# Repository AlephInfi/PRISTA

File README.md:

# PRISTA
Development repository for PRISTA (PC/104 and RS-485 Integration with Sensors Testing Assembly)

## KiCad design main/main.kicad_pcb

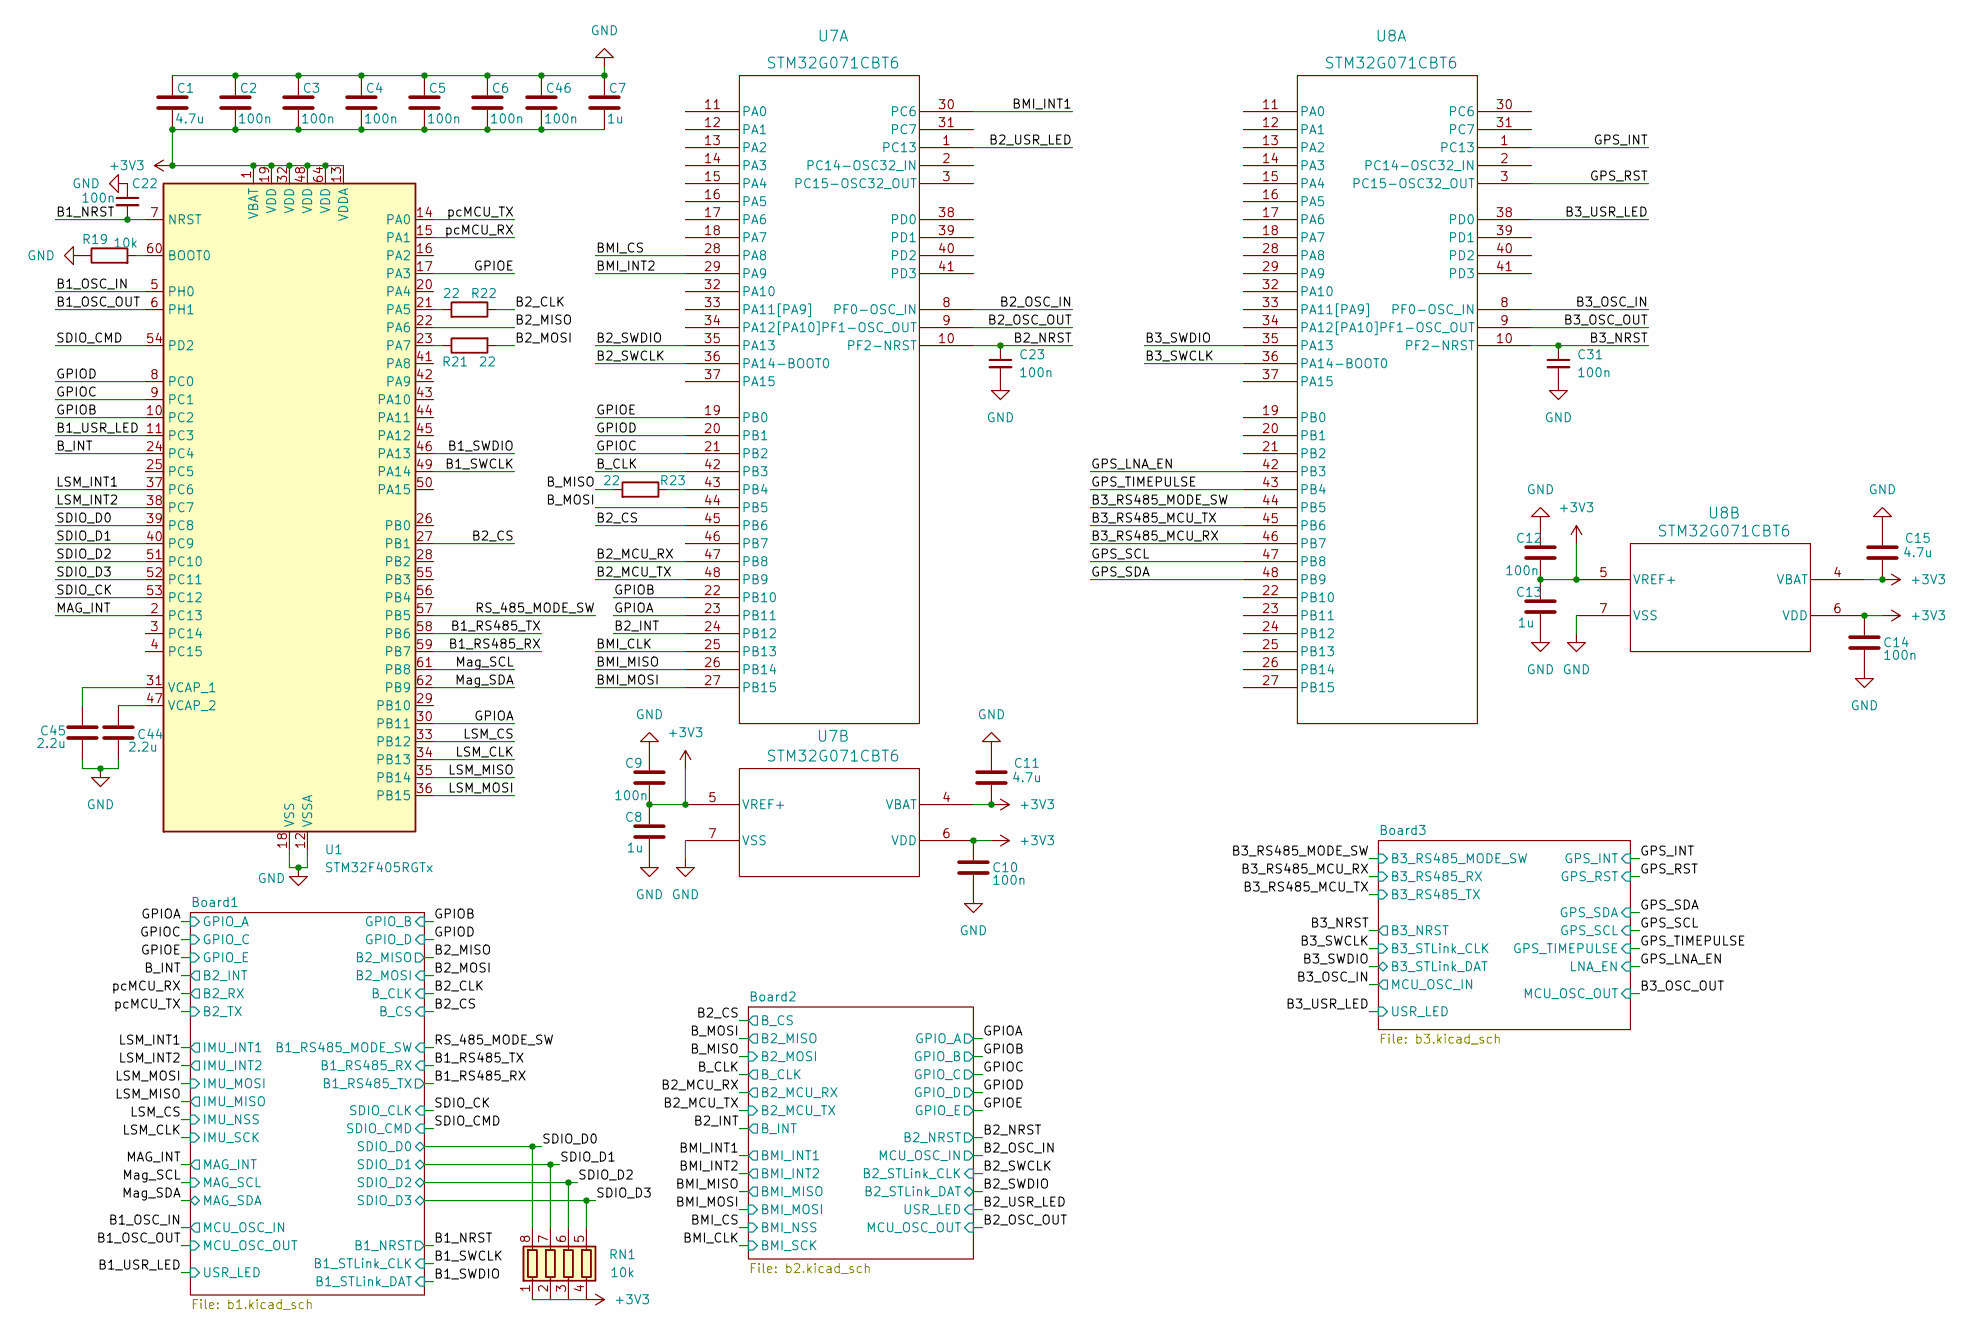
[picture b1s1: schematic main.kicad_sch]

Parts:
C1, C11, C15: 4.7u; C_0603_1608Metric
C2, C3, C4, C5, C6, C9, C10, C12, C14, C22, C23, C31, C46: 100n; C_0603_1608Metric
C7, C8, C13: 1u; C_0603_1608Metric
C44, C45: 2.2u; C_0603_1608Metric
R19: 10k; R_0603_1608Metric
R21, R22, R23: 22; R_0603_1608Metric; LCSC C23345
RN1: 10k; R_Array_Convex_4x0603; MPN UNI-ROYAL 4D03WGJ0103T5E; LCSC C29718
U1: STM32F405RGTx; LQFP-64_10x10mm_P0.5mm
U7, U8: STM32G071CBT6; LQFP-48_7x7mm_P0.5mm

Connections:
+3V3: C1.2, C2.2, C3.2, C4.2, C5.2, C6.2, C7.2, C8.1, C9.2, C10.1, C11.2, C12.2, C13.1, C14.1, C15.2, C46.2, RN1.1 (R1.1), RN1.2 (R2.1), RN1.3 (R3.1), RN1.4 (R4.1), U1.1 (VBAT), U1.13 (VDDA), U1.19 (VDD), U1.32 (VDD), U1.48 (VDD), U1.64 (VDD), U7.4 (VBAT), U7.5 (VREF+), U7.6 (VDD), U8.4 (VBAT), U8.5 (VREF+), U8.6 (VDD); also elsewhere on the board
/B1_NRST: C22.2, U1.7 (NRST); also elsewhere on the board
/B1_OSC_IN: U1.5 (PH0); also elsewhere on the board
/B1_OSC_OUT: U1.6 (PH1); also elsewhere on the board
/B1_RS485_RX: U1.59 (PB7); also elsewhere on the board
/B1_RS485_TX: U1.58 (PB6); also elsewhere on the board
/B1_SWCLK: U1.49 (PA14); also elsewhere on the board
/B1_SWDIO: U1.46 (PA13); also elsewhere on the board
/B1_USR_LED: U1.11 (PC3); also elsewhere on the board
/B2_CLK: R22.1; also elsewhere on the board
/B2_CS: U1.27 (PB1), U7.45 (PB6); also elsewhere on the board
/B2_INT: U7.24 (PB12); also elsewhere on the board
/B2_MCU_RX: U7.47 (PB8); also elsewhere on the board
/B2_MCU_TX: U7.48 (PB9); also elsewhere on the board
/B2_MISO: U1.22 (PA6); also elsewhere on the board
/B2_MOSI: R21.2; also elsewhere on the board
/B2_NRST: C23.1, U7.10 (PF2-NRST); also elsewhere on the board
/B2_OSC_IN: U7.8 (PF0-OSC_IN); also elsewhere on the board
/B2_OSC_OUT: U7.9 (PF1-OSC_OUT); also elsewhere on the board
/B2_SWCLK: U7.36 (PA14-BOOT0); also elsewhere on the board
/B2_SWDIO: U7.35 (PA13); also elsewhere on the board
/B2_USR_LED: U7.1 (PC13); also elsewhere on the board
/B3_NRST: C31.1, U8.10 (PF2-NRST); also elsewhere on the board
/B3_OSC_IN: U8.8 (PF0-OSC_IN); also elsewhere on the board
/B3_OSC_OUT: U8.9 (PF1-OSC_OUT); also elsewhere on the board
/B3_RS485_MCU_RX: U8.46 (PB7); also elsewhere on the board
/B3_RS485_MCU_TX: U8.45 (PB6); also elsewhere on the board
/B3_RS485_MODE_SW: U8.44 (PB5); also elsewhere on the board
/B3_SWCLK: U8.36 (PA14-BOOT0); also elsewhere on the board
/B3_SWDIO: U8.35 (PA13); also elsewhere on the board
/B3_USR_LED: U8.38 (PD0); also elsewhere on the board
/BMI_CLK: U7.25 (PB13); also elsewhere on the board
/BMI_CS: U7.28 (PA8); also elsewhere on the board
/BMI_INT1: U7.30 (PC6); also elsewhere on the board
/BMI_INT2: U7.29 (PA9); also elsewhere on the board
/BMI_MISO: U7.26 (PB14); also elsewhere on the board
/BMI_MOSI: U7.27 (PB15); also elsewhere on the board
/B_CLK: U7.42 (PB3); also elsewhere on the board
/B_INT: U1.24 (PC4); also elsewhere on the board
/B_MISO: R23.2; also elsewhere on the board
/B_MOSI: U7.44 (PB5); also elsewhere on the board
/GPIOA: U1.30 (PB11), U7.23 (PB11); also elsewhere on the board
/GPIOB: U1.10 (PC2), U7.22 (PB10); also elsewhere on the board
/GPIOC: U1.9 (PC1), U7.21 (PB2); also elsewhere on the board
/GPIOD: U1.8 (PC0), U7.20 (PB1); also elsewhere on the board
/GPIOE: U1.17 (PA3), U7.19 (PB0); also elsewhere on the board
/GPS_INT: U8.1 (PC13); also elsewhere on the board
/GPS_LNA_EN: U8.42 (PB3); also elsewhere on the board
/GPS_RST: U8.3 (PC15-OSC32_OUT); also elsewhere on the board
/GPS_SCL: U8.47 (PB8); also elsewhere on the board
/GPS_SDA: U8.48 (PB9); also elsewhere on the board
/GPS_TIMEPULSE: U8.43 (PB4); also elsewhere on the board
/LSM_CLK: U1.34 (PB13); also elsewhere on the board
/LSM_CS: U1.33 (PB12); also elsewhere on the board
/LSM_INT1: U1.37 (PC6); also elsewhere on the board
/LSM_INT2: U1.38 (PC7); also elsewhere on the board
/LSM_MISO: U1.35 (PB14); also elsewhere on the board
/LSM_MOSI: U1.36 (PB15); also elsewhere on the board
/MAG_INT: U1.2 (PC13); also elsewhere on the board
/Mag_SCL: U1.61 (PB8); also elsewhere on the board
/Mag_SDA: U1.62 (PB9); also elsewhere on the board
/RS_485_MODE_SW: U1.57 (PB5); also elsewhere on the board
/SDIO_CK: U1.53 (PC12); also elsewhere on the board
/SDIO_CMD: U1.54 (PD2); also elsewhere on the board
/SDIO_D0: RN1.8 (R1.2), U1.39 (PC8); also elsewhere on the board
/SDIO_D1: RN1.7 (R2.2), U1.40 (PC9); also elsewhere on the board
/SDIO_D2: RN1.6 (R3.2), U1.51 (PC10); also elsewhere on the board
/SDIO_D3: RN1.5 (R4.2), U1.52 (PC11); also elsewhere on the board
/pcMCU_RX: U1.15 (PA1); also elsewhere on the board
/pcMCU_TX: U1.14 (PA0); also elsewhere on the board
GND: C1.1, C2.1, C3.1, C4.1, C5.1, C6.1, C7.1, C8.2, C9.1, C10.2, C11.1, C12.1, C13.2, C14.2, C15.1, C22.1, C23.2, C31.2, C44.2, C45.2, C46.1, R19.1, U1.12 (VSSA), U1.18 (VSS), U1.63 (VSS), U7.7 (VSS), U8.7 (VSS); also elsewhere on the board
unnamed: R19.2, U1.60 (BOOT0)
unnamed: R22.2, U1.21 (PA5)
unnamed: R21.1, U1.23 (PA7)
unnamed: C45.1, U1.31 (VCAP_1)
unnamed: C44.1, U1.47 (VCAP_2)
unnamed: R23.1, U7.43 (PB4)

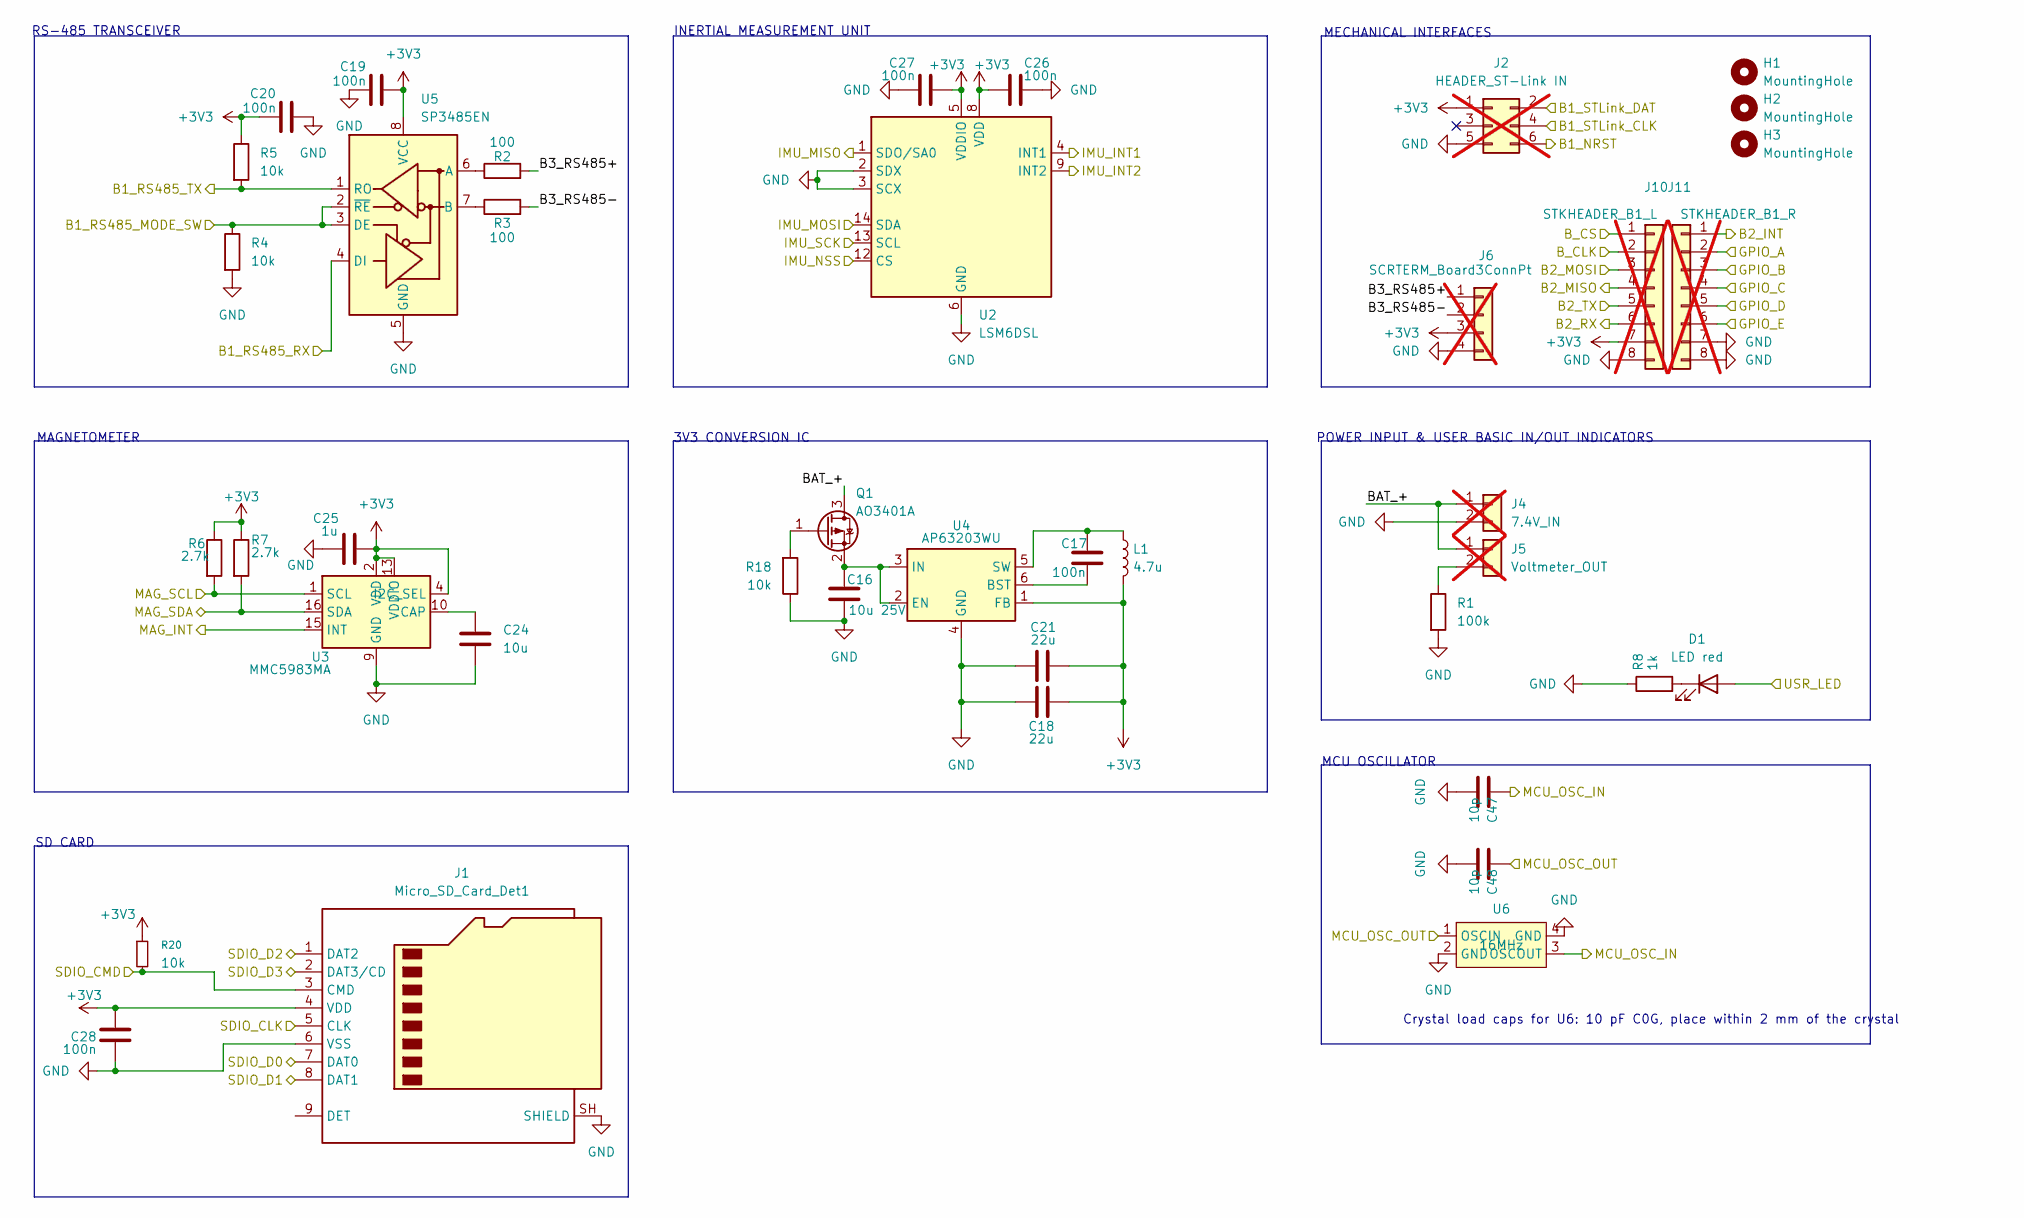
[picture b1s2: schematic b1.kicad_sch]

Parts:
C16: 10u 25V; C_0805_2012Metric; LCSC C15850
C17, C19, C20, C26, C27, C28: 100n; C_0603_1608Metric
C18, C21: 22u; C_0603_1608Metric; LCSC C59461
C24: 10u; C_0603_1608Metric
C25: 1u; C_0603_1608Metric
C47, C48: 10p; C_0603_1608Metric; LCSC C1634
D1: LED red; LED_0805_2012Metric; LCSC C84256
H1, H2, H3: MountingHole; MountingHole_3.2mm_M3
J1: Micro_SD_Card_Det1; microSD_HC_Molex_47219-2001
J2: HEADER_ST-Link IN; PinHeader_2x03_P2.54mm_Horizontal; not fitted
J4: 7.4V_IN; TerminalBlock_Phoenix_MKDS-1-2-3.81_1x02_P3.81mm_Horizontal; not fitted
J5: Voltmeter_OUT; TerminalBlock_Phoenix_MKDS-1-2-3.81_1x02_P3.81mm_Horizontal; not fitted
J6: SCRTERM_Board3ConnPt; TerminalBlock_Phoenix_MKDS-1-4-3.81_1x04_P3.81mm_Horizontal; not fitted
J10: STKHEADER_B1_R; PinHeader_1x08_P2.54mm_Vertical; not fitted
J11: STKHEADER_B1_L; PinHeader_1x08_P2.54mm_Vertical; not fitted
L1: 4.7u; L_6.3x6.3_H3
Q1: AO3401A; SOT-23; LCSC C15127
R1: 100k; R_0603_1608Metric
R2, R3: 100; R_0603_1608Metric
R4, R5, R18, R20: 10k; R_0603_1608Metric
R6, R7: 2.7k; R_0603_1608Metric
R8: 1k; R_0603_1608Metric
U2: LSM6DSL; LGA-14_3x2.5mm_P0.5mm_LayoutBorder3x4y
U3: MMC5983MA; LGA-16_3x3mm_P0.5mm
U4: AP63203WU; TSOT-23-6
U5: SP3485EN; SOIC-8_3.9x4.9mm_P1.27mm; LCSC C8963
U6: 16MHz; Crystal_SMD_3225-4Pin_3.2x2.5mm; MPN YXC X322516MLB4SI; LCSC C13738

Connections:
+3V3: C18.1, C19.2, C20.1, C21.1, C25.2, C26.1, C27.2, C28.1, J1.4 (VDD), J2.1, J6.3, J10.7, L1.2, R5.1, R6.1, R7.1, R20.1, U2.5 (VDDIO), U2.8 (VDD), U3.2 (VDD), U3.4 (I2C_SEL), U3.13 (VDDIO), U4.1 (FB), U5.8 (VCC); also elsewhere on the board
/B1_NRST: J2.6; also elsewhere on the board
/B1_OSC_IN: C47.1, U6.3 (OSCOUT); also elsewhere on the board
/B1_OSC_OUT: C48.1, U6.1 (OSCIN); also elsewhere on the board
/B1_RS485_RX: R5.2, U5.1 (RO); also elsewhere on the board
/B1_RS485_TX: U5.4 (DI); also elsewhere on the board
/B1_SWCLK: J2.4; also elsewhere on the board
/B1_SWDIO: J2.2; also elsewhere on the board
/B1_USR_LED: D1.2 (A); also elsewhere on the board
/B2_CLK: J10.2; also elsewhere on the board
/B2_CS: J10.1; also elsewhere on the board
/B2_MISO: J10.4; also elsewhere on the board
/B2_MOSI: J10.3; also elsewhere on the board
/B_INT: J11.1; also elsewhere on the board
/Board1/B3_RS485+: J6.1, R2.2
/Board1/B3_RS485-: J6.2, R3.2
/Board1/BAT_+: J4.1, J5.1, Q1.3 (D)
/GPIOA: J11.2; also elsewhere on the board
/GPIOB: J11.3; also elsewhere on the board
/GPIOC: J11.4; also elsewhere on the board
/GPIOD: J11.5; also elsewhere on the board
/GPIOE: J11.6; also elsewhere on the board
/LSM_CLK: U2.13 (SCL); also elsewhere on the board
/LSM_CS: U2.12 (CS); also elsewhere on the board
/LSM_INT1: U2.4 (INT1); also elsewhere on the board
/LSM_INT2: U2.9 (INT2); also elsewhere on the board
/LSM_MISO: U2.1 (SDO/SA0); also elsewhere on the board
/LSM_MOSI: U2.14 (SDA); also elsewhere on the board
/MAG_INT: U3.15 (INT); also elsewhere on the board
/Mag_SCL: R6.2, U3.1 (SCL); also elsewhere on the board
/Mag_SDA: R7.2, U3.16 (SDA); also elsewhere on the board
/RS_485_MODE_SW: R4.1, U5.2 (~RE), U5.3 (DE); also elsewhere on the board
/SDIO_CK: J1.5 (CLK); also elsewhere on the board
/SDIO_CMD: J1.3 (CMD), R20.2; also elsewhere on the board
/SDIO_D0: J1.7 (DAT0); also elsewhere on the board
/SDIO_D1: J1.8 (DAT1); also elsewhere on the board
/SDIO_D2: J1.1 (DAT2); also elsewhere on the board
/SDIO_D3: J1.2 (DAT3/CD); also elsewhere on the board
/pcMCU_RX: J10.6; also elsewhere on the board
/pcMCU_TX: J10.5; also elsewhere on the board
GND: C16.2, C18.2, C19.1, C20.2, C21.2, C24.2, C25.1, C26.2, C27.1, C28.2, C47.2, C48.2, J1.6 (VSS), J1.SH (SHIELD), J2.5, J4.2, J6.4, J10.8, J11.7, J11.8, R1.2, R4.2, R8.1, R18.1, U2.2 (SDX), U2.3 (SCX), U2.6 (GND), U2.7 (GND), U3.9 (GND), U3.11 (GND), U4.4 (GND), U5.5 (GND), U6.2 (GND), U6.4 (GND); also elsewhere on the board
unnamed: D1.1 (K), R8.2
unnamed: J5.2, R1.1
unnamed: Q1.1 (G), R18.2
unnamed: C16.1, Q1.2 (S), U4.2 (EN), U4.3 (IN)
unnamed: C24.1, U3.10 (CAP)
unnamed: C17.2, U4.6 (BST)
unnamed: C17.1, L1.1, U4.5 (SW)
unnamed: R2.1, U5.6 (A)
unnamed: R3.1, U5.7 (B)

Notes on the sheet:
INERTIAL MEASUREMENT UNIT
MAGNETOMETER
Crystal load caps for U6: 10 pF C0G, place within 2 mm of the crystal
POWER INPUT & USER BASIC IN/OUT INDICATORS
MCU OSCILLATOR
RS-485 TRANSCEIVER
SD CARD
3V3 CONVERSION IC
MECHANICAL INTERFACES

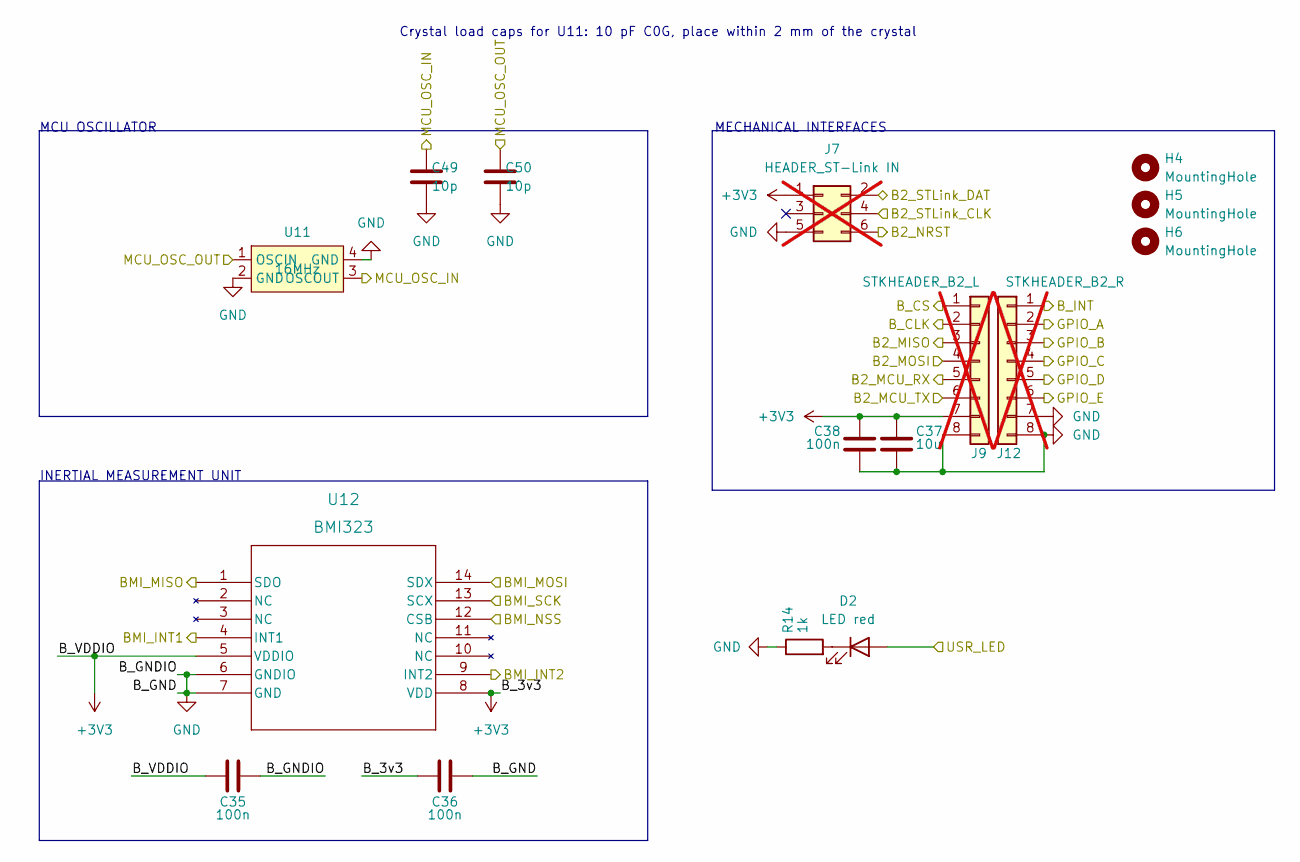
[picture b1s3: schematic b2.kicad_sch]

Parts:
C35, C36, C38: 100n; C_0603_1608Metric
C37: 10u; C_0603_1608Metric
C49, C50: 10p; C_0603_1608Metric; LCSC C1634
D2: LED red; LED_0805_2012Metric; LCSC C84256
H4, H5, H6: MountingHole; MountingHole_3.2mm_M3
J7: HEADER_ST-Link IN; PinHeader_2x03_P2.54mm_Horizontal; not fitted
J9: STKHEADER_B2_L; PinSocket_1x08_P2.54mm_Vertical; not fitted
J12: STKHEADER_B2_R; PinSocket_1x08_P2.54mm_Vertical; not fitted
R14: 1k; R_0603_1608Metric
U11: 16MHz; Crystal_SMD_3225-4Pin_3.2x2.5mm; MPN YXC X322516MLB4SI; LCSC C13738
U12: BMI323; BMI323_BOS

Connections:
+3V3: C35.1, C36.1, C37.1, C38.1, J7.1, J9.7, U12.5 (VDDIO), U12.8 (VDD); also elsewhere on the board
/B2_CS: J9.1; also elsewhere on the board
/B2_INT: J12.1; also elsewhere on the board
/B2_MCU_RX: J9.5; also elsewhere on the board
/B2_MCU_TX: J9.6; also elsewhere on the board
/B2_NRST: J7.6; also elsewhere on the board
/B2_OSC_IN: C49.1, U11.3 (OSCOUT); also elsewhere on the board
/B2_OSC_OUT: C50.1, U11.1 (OSCIN); also elsewhere on the board
/B2_SWCLK: J7.4; also elsewhere on the board
/B2_SWDIO: J7.2; also elsewhere on the board
/B2_USR_LED: D2.2 (A); also elsewhere on the board
/BMI_CLK: U12.13 (SCX); also elsewhere on the board
/BMI_CS: U12.12 (CSB); also elsewhere on the board
/BMI_INT1: U12.4 (INT1); also elsewhere on the board
/BMI_INT2: U12.9 (INT2); also elsewhere on the board
/BMI_MISO: U12.1 (SDO); also elsewhere on the board
/BMI_MOSI: U12.14 (SDX); also elsewhere on the board
/B_CLK: J9.2; also elsewhere on the board
/B_MISO: J9.4; also elsewhere on the board
/B_MOSI: J9.3; also elsewhere on the board
/GPIOA: J12.2; also elsewhere on the board
/GPIOB: J12.3; also elsewhere on the board
/GPIOC: J12.4; also elsewhere on the board
/GPIOD: J12.5; also elsewhere on the board
/GPIOE: J12.6; also elsewhere on the board
GND: C35.2, C36.2, C37.2, C38.2, C49.2, C50.2, J7.5, J9.8, J12.7, J12.8, R14.1, U11.2 (GND), U11.4 (GND), U12.6 (GNDIO), U12.7 (GND); also elsewhere on the board
unnamed: D2.1 (K), R14.2

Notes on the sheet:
INERTIAL MEASUREMENT UNIT
MCU OSCILLATOR
Crystal load caps for U11: 10 pF C0G, place within 2 mm of the crystal
MECHANICAL INTERFACES

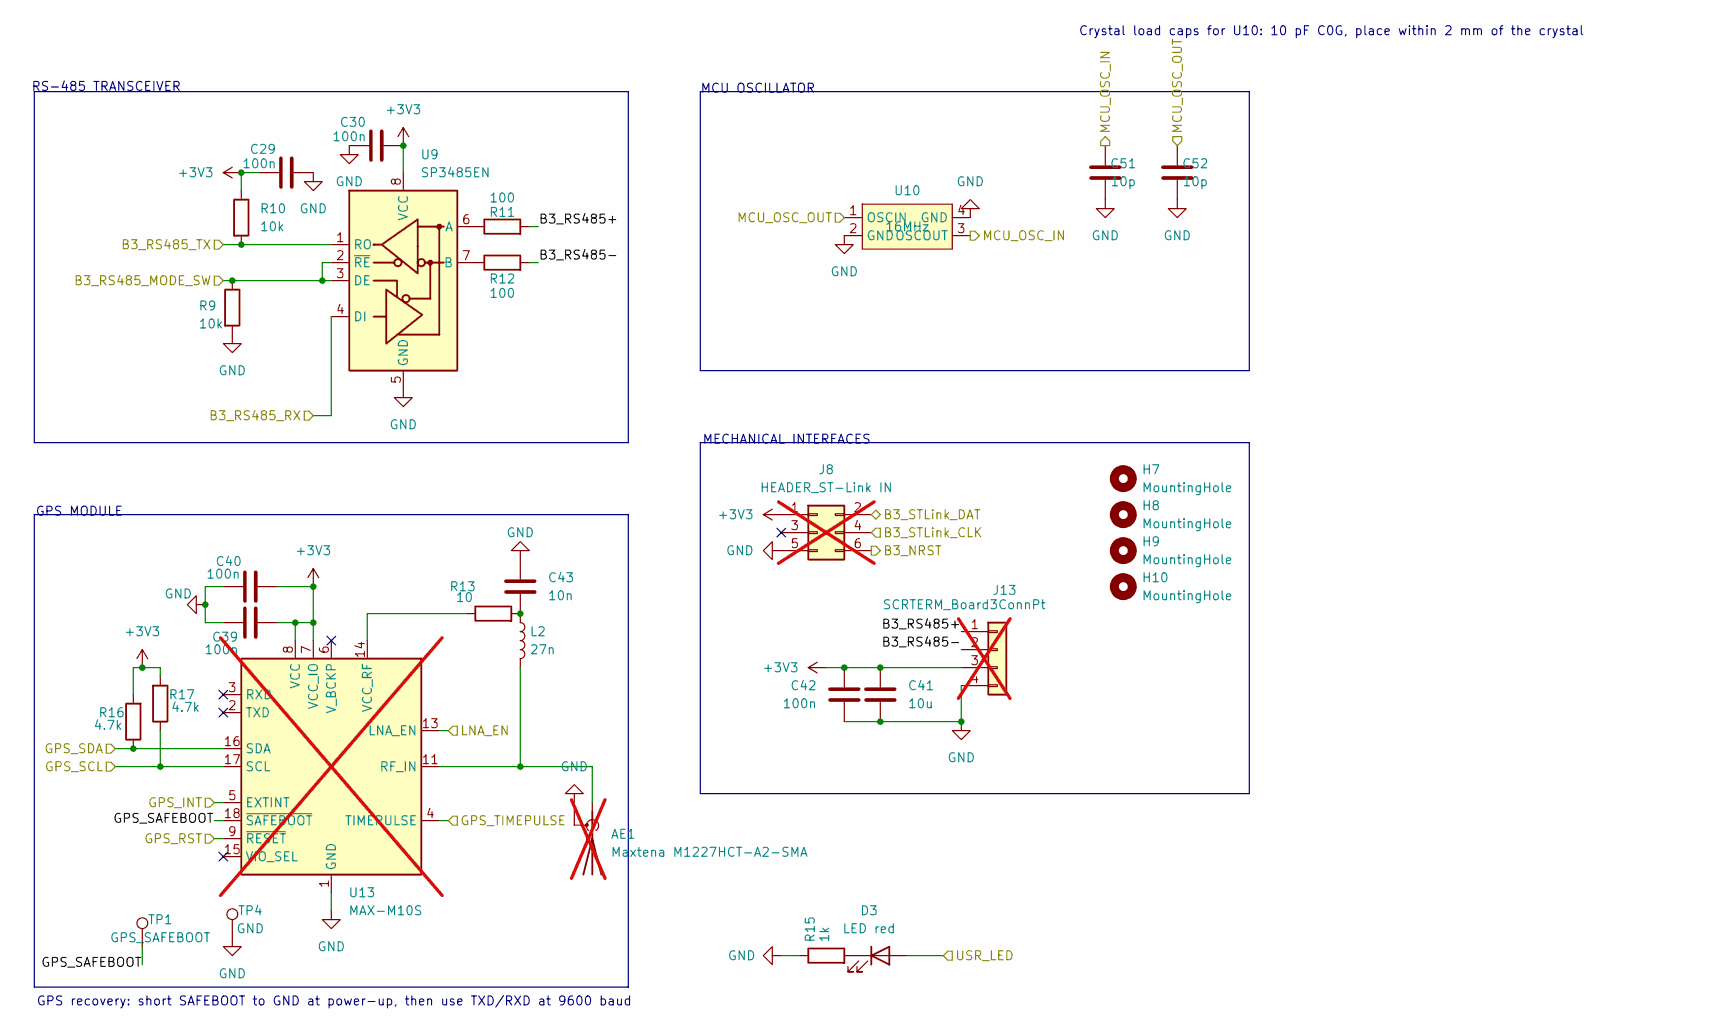
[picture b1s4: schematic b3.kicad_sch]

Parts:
AE1: Maxtena M1227HCT-A2-SMA; SMA_Amphenol_132289_EdgeMount; not fitted
C29, C30, C39, C40, C42: 100n; C_0603_1608Metric
C41: 10u; C_0603_1608Metric
C43: 10n; C_0603_1608Metric
C51, C52: 10p; C_0603_1608Metric; LCSC C1634
D3: LED red; LED_0805_2012Metric; LCSC C84256
H7, H8, H9, H10: MountingHole; MountingHole_3.2mm_M3
J8: HEADER_ST-Link IN; PinHeader_2x03_P2.54mm_Horizontal; not fitted
J13: SCRTERM_Board3ConnPt; TerminalBlock_Phoenix_MKDS-1-4-3.81_1x04_P3.81mm_Horizontal; not fitted
L2: 27n; L_0603_1608Metric
R9, R10: 10k; R_0603_1608Metric
R11, R12: 100; R_0603_1608Metric
R13: 10; R_0603_1608Metric
R15: 1k; R_0603_1608Metric
R16, R17: 4.7k; R_0603_1608Metric
TP1: GPS_SAFEBOOT; TestPoint_Pad_D1.0mm
TP4: GND; TestPoint_Pad_D1.0mm
U9: SP3485EN; SOIC-8_3.9x4.9mm_P1.27mm; LCSC C8963
U10: 16MHz; Crystal_SMD_3225-4Pin_3.2x2.5mm; MPN YXC X322516MLB4SI; LCSC C13738
U13: MAX-M10S; ublox_MAX; not fitted

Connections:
+3V3: C29.1, C30.2, C39.1, C40.1, C41.1, C42.1, J8.1, J13.3, R10.1, R16.2, R17.2, U9.8 (VCC), U13.7 (VCC_IO), U13.8 (VCC); also elsewhere on the board
/B3_NRST: J8.6; also elsewhere on the board
/B3_OSC_IN: C51.1, U10.3 (OSCOUT); also elsewhere on the board
/B3_OSC_OUT: C52.1, U10.1 (OSCIN); also elsewhere on the board
/B3_RS485_MCU_RX: U9.4 (DI); also elsewhere on the board
/B3_RS485_MCU_TX: R10.2, U9.1 (RO); also elsewhere on the board
/B3_RS485_MODE_SW: R9.1, U9.2 (~RE), U9.3 (DE); also elsewhere on the board
/B3_SWCLK: J8.4; also elsewhere on the board
/B3_SWDIO: J8.2; also elsewhere on the board
/B3_USR_LED: D3.2 (A); also elsewhere on the board
/Board3/B3_RS485+: J13.1, R11.2
/Board3/B3_RS485-: J13.2, R12.2
/Board3/GPS_SAFEBOOT: TP1.1 (1_1), U13.18 (~SAFEBOOT)
/GPS_INT: U13.5 (EXTINT); also elsewhere on the board
/GPS_LNA_EN: U13.13 (LNA_EN); also elsewhere on the board
/GPS_RST: U13.9 (~RESET); also elsewhere on the board
/GPS_SCL: R17.1, U13.17 (SCL); also elsewhere on the board
/GPS_SDA: R16.1, U13.16 (SDA); also elsewhere on the board
/GPS_TIMEPULSE: U13.4 (TIMEPULSE); also elsewhere on the board
GND: AE1.2 (Shield), C29.2, C30.1, C39.2, C40.2, C41.2, C42.2, C43.1, C51.2, C52.2, J8.5, J13.4, R9.2, R15.1, TP4.1 (1_1), U9.5 (GND), U10.2 (GND), U10.4 (GND), U13.1 (GND), U13.10 (GND), U13.12 (GND); also elsewhere on the board
unnamed: AE1.1 (A), L2.2, U13.11 (RF_IN)
unnamed: C43.2, L2.1, R13.2
unnamed: D3.1 (K), R15.2
unnamed: R11.1, U9.6 (A)
unnamed: R12.1, U9.7 (B)
unnamed: R13.1, U13.14 (VCC_RF)

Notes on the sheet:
RS-485 TRANSCEIVER
GPS MODULE
Crystal load caps for U10: 10 pF C0G, place within 2 mm of the crystal
GPS recovery: short SAFEBOOT to GND at power-up, then use TXD/RXD at 9600 baud
MECHANICAL INTERFACES
MCU OSCILLATOR

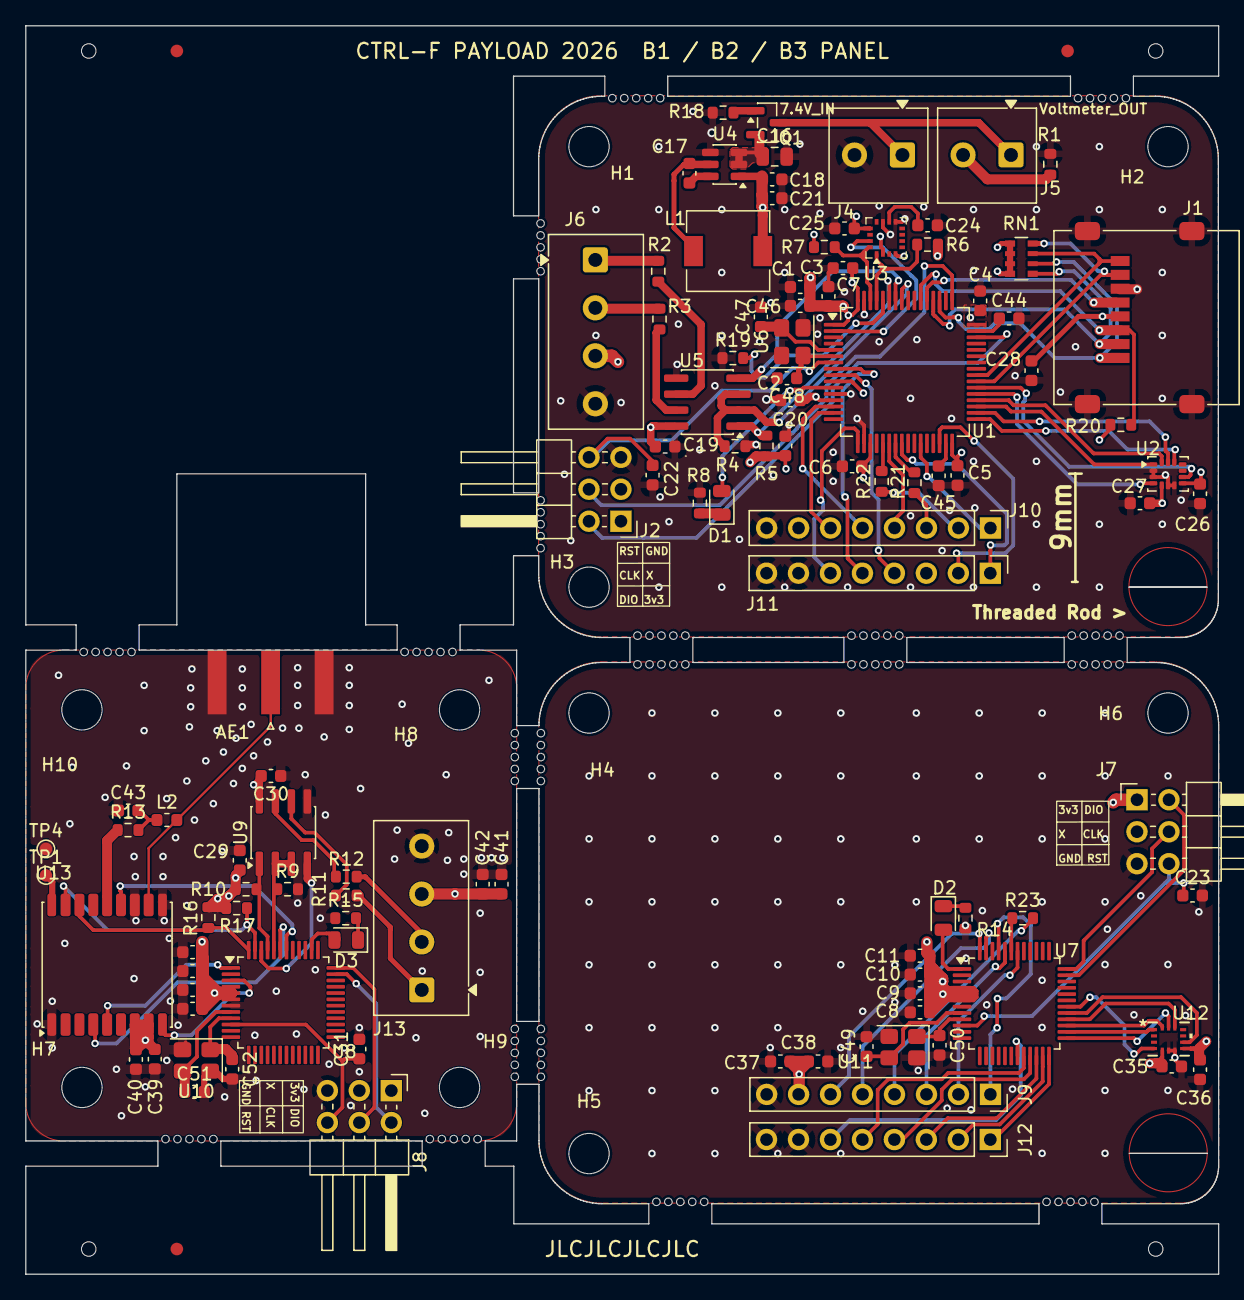
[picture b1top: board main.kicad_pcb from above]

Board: 4 copper layers, 94.8 x 99.2 mm, 139 parts (0 on the bottom side), 99 nets.

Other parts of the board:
FID1, FID2, FID3: Fiducial; Fiducial_1mm_Mask2mm
MB1: R-B1a; MouseBite
MB2: R-B1b; MouseBite
MB3: F-B1a; MouseBite
MB4: F-B1b; MouseBite
MB5: B1-B2a; MouseBite
MB6: B1-B2b; MouseBite
MB7: B1-B2c; MouseBite
MB8: B2-Ra; MouseBite
MB9: B2-Rb; MouseBite
MB10: B3-B2a; MouseBite
MB11: B3-B2b; MouseBite
MB12: F-B3a; MouseBite
MB13: F-B3b; MouseBite
MB14: B3-Fa; MouseBite
MB15: B3-Fb; MouseBite
TH1, TH2, TH3, TH4: Tooling; ToolingHole_1.152mm

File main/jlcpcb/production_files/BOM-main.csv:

Comment,Designator,Footprint,LCSC,Quantity
10,R13,R_0603_1608Metric,C22859,1
100,"R11,R12,R2,R3",R_0603_1608Metric,C22775,4
100k,R1,R_0603_1608Metric,C25803,1
100n,"C10,C12,C14,C17,C19,C2,C20,C22,C23,C26,C27,C28,C29,C3,C30,C31,C35,C36,C38,C39,C4,C40,C42,C46,C5,C6,C9",C_0603_1608Metric,C14663,27
10k,"R10,R18,R19,R20,R4,R5,R9",R_0603_1608Metric,C25804,7
10k,RN1,R_Array_Convex_4x0603,C29718,1
10n,C43,C_0603_1608Metric,C57112,1
10p,"C47,C48,C49,C50,C51,C52",C_0603_1608Metric,C1634,6
10u,"C24,C37,C41",C_0603_1608Metric,C19702,3
10u 25V,C16,C_0805_2012Metric,C15850,1
16MHz,"U10,U11,U6",Crystal_SMD_3225-4Pin_3.2x2.5mm,C13738,3
1k,"R14,R15,R8",R_0603_1608Metric,C21190,3
1u,"C13,C25,C7,C8",C_0603_1608Metric,C15849,4
2.2u,"C44,C45",C_0603_1608Metric,C23630,2
2.7k,"R6,R7",R_0603_1608Metric,C13167,2
22,"R21,R22,R23",R_0603_1608Metric,C23345,3
22u,"C18,C21",C_0603_1608Metric,C59461,2
27n,L2,L_0603_1608Metric,C12669,1
4.7k,"R16,R17",R_0603_1608Metric,C23162,2
4.7u,L1,L_6.3x6.3_H3,C128688,1
4.7u,"C1,C11,C15",C_0603_1608Metric,C19666,3
AO3401A,Q1,SOT-23,C15127,1
AP63203WU,U4,TSOT-23-6,C780769,1
BMI323,U12,BMI323_BOS,C5368700,1
LED red,"D1,D2,D3",LED_0805_2012Metric,C84256,3
LSM6DSL,U2,LGA-14_3x2.5mm_P0.5mm_LayoutBorder3x4y,C126672,1
MMC5983MA,U3,LGA-16_3x3mm_P0.5mm,C404329,1
Micro_SD_Card_Det1,J1,microSD_HC_Molex_47219-2001,C164170,1
SP3485EN,"U5,U9",SOIC-8_3.9x4.9mm_P1.27mm,C8963,2
STM32F405RGTx,U1,LQFP-64_10x10mm_P0.5mm,C15742,1
STM32G071CBT6,"U7,U8",LQFP-48_7x7mm_P0.5mm,C432212,2

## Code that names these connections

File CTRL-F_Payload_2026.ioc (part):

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Mcu.Name=STM32F405RGTx
Mcu.Package=LQFP64
Mcu.UserName=STM32F405RGTx
PA0-WKUP.GPIOParameters=GPIO_Label
PA0-WKUP.GPIO_Label=PCTX
PA0-WKUP.Mode=Asynchronous
PA0-WKUP.Signal=UART4_TX
PA1.GPIOParameters=GPIO_Label
PA1.GPIO_Label=PCRX
PA1.Mode=Asynchronous
PA1.Signal=UART4_RX
PA13.Mode=Serial_Wire
PA13.Signal=SYS_JTMS-SWDIO
PA14.Mode=Serial_Wire
PA14.Signal=SYS_JTCK-SWCLK
PA15.GPIOParameters=GPIO_Label
PA15.GPIO_Label=SD_Detect
PA15.Signal=GPXTI15
PA3.GPIOParameters=GPIO_Label
PA3.GPIO_Label=GPIO_E
PA3.Signal=GPIO_Output
PA5.GPIOParameters=GPIO_Label
PA5.GPIO_Label=B2_CLK
PA5.Mode=Full_Duplex_Master
PA5.Signal=SPI1_SCK
PA6.GPIOParameters=GPIO_Label
PA6.GPIO_Label=B2_MISO
PA6.Mode=Full_Duplex_Master
PA6.Signal=SPI1_MISO
PA7.GPIOParameters=GPIO_Label
PA7.GPIO_Label=B2_MOSI
PA7.Mode=Full_Duplex_Master
PA7.Signal=SPI1_MOSI
PB1.GPIOParameters=GPIO_Label
PB1.GPIO_Label=B2_CS
PB1.Signal=GPIO_Output
PB11.GPIOParameters=GPIO_Label
PB11.GPIO_Label=GPIO_A
PB11.Signal=GPIO_Output
PB12.GPIOParameters=GPIO_Label
PB12.GPIO_Label=LSM_CS
PB12.Signal=GPIO_Output
PB13.GPIOParameters=GPIO_Label
PB13.GPIO_Label=LSM_CLK
PB13.Mode=Full_Duplex_Master
PB13.Signal=SPI2_SCK
PB14.GPIOParameters=GPIO_Label
PB14.GPIO_Label=LSM_MISO
PB14.Mode=Full_Duplex_Master
PB14.Signal=SPI2_MISO
PB15.GPIOParameters=GPIO_Label
PB15.GPIO_Label=LSM_MOSI
PB15.Mode=Full_Duplex_Master
PB15.Signal=SPI2_MOSI
PB5.GPIOParameters=GPIO_Label
PB5.GPIO_Label=RS485_MODE_SW
PB5.Signal=GPIO_Output
PB6.GPIOParameters=GPIO_Label
PB6.GPIO_Label=RS485_TX
PB6.Mode=Asynchronous
PB6.Signal=USART1_TX
PB7.GPIOParameters=GPIO_Label
PB7.GPIO_Label=RS485_RX
PB7.Mode=Asynchronous
PB7.Signal=USART1_RX
PB8.GPIOParameters=GPIO_Label
PB8.GPIO_Label=MAG_SCL
PB8.Mode=I2C
PB8.Signal=I2C1_SCL
PB9.GPIOParameters=GPIO_Label
PB9.GPIO_Label=MAG_SDA
PB9.Mode=I2C
PB9.Signal=I2C1_SDA
PC0.GPIOParameters=GPIO_Label
PC0.GPIO_Label=GPIO_D
PC0.Signal=GPIO_Input
PC1.GPIOParameters=GPIO_Label
PC1.GPIO_Label=GPIO_C
PC1.Signal=GPIO_Input
PC10.Mode=SD_4_bits_Wide_bus
PC10.Signal=SDIO_D2
PC11.Mode=SD_4_bits_Wide_bus
PC11.Signal=SDIO_D3
PC12.Mode=SD_4_bits_Wide_bus
PC12.Signal=SDIO_CK
PC13-ANTI_TAMP.GPIOParameters=GPIO_Label
PC13-ANTI_TAMP.GPIO_Label=MAG_INT
PC13-ANTI_TAMP.Signal=GPIO_Input
PC2.GPIOParameters=GPIO_Label
PC2.GPIO_Label=GPIO_B
PC2.Signal=GPIO_Input
PC3.GPIOParameters=GPIO_Label
PC3.GPIO_Label=USR_LED
PC3.Signal=GPIO_Output
PC4.GPIOParameters=GPIO_Label
PC4.GPIO_Label=B2_INT
PC4.Signal=GPIO_Input
PC6.GPIOParameters=GPIO_Label
PC6.GPIO_Label=LSM_INT1
PC6.Signal=GPIO_Input
PC7.GPIOParameters=GPIO_Label
PC7.GPIO_Label=LSM_INT2
PC7.Signal=GPIO_Input
PC8.Mode=SD_4_bits_Wide_bus
PC8.Signal=SDIO_D0
PC9.Mode=SD_4_bits_Wide_bus
PC9.Signal=SDIO_D1
PD2.Mode=SD_4_bits_Wide_bus
PD2.Signal=SDIO_CMD
PH0-OSC_IN.Mode=HSE-External-Oscillator
PH0-OSC_IN.Signal=RCC_OSC_IN
PH1-OSC_OUT.Mode=HSE-External-Oscillator
PH1-OSC_OUT.Signal=RCC_OSC_OUT
RCC.HSE_VALUE=25000000
RCC.SYSCLKFreq_VALUE=16000000
board=custom

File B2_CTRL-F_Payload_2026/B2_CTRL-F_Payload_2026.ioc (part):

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Mcu.Name=STM32G071C(6-8-B)Tx
Mcu.Package=LQFP48
Mcu.UserName=STM32G071CBTx
PA13.Mode=Serial_Wire
PA13.Signal=SYS_SWDIO
PA14-BOOT0.Mode=Serial_Wire
PA14-BOOT0.Signal=SYS_SWCLK
PA8.GPIOParameters=GPIO_Label
PA8.GPIO_Label=BMI_CS
PA8.Signal=GPIO_Output
PA9.GPIOParameters=GPIO_Label
PA9.GPIO_Label=BMI_INT2
PA9.Signal=GPIO_Input
PB0.GPIOParameters=GPIO_Label
PB0.GPIO_Label=E
PB0.Signal=GPIO_Input
PB1.GPIOParameters=GPIO_Label
PB1.GPIO_Label=D
PB1.Signal=GPIO_Input
PB10.GPIOParameters=GPIO_Label
PB10.GPIO_Label=B
PB10.Signal=GPIO_Input
PB11.GPIOParameters=GPIO_Label
PB11.GPIO_Label=A
PB11.Signal=GPIO_Input
PB12.GPIOParameters=GPIO_Label
PB12.GPIO_Label=B2_INT
PB12.Signal=GPIO_Output
PB13.GPIOParameters=GPIO_Label
PB13.GPIO_Label=BMI_CLK
PB13.Mode=Full_Duplex_Master
PB13.Signal=SPI2_SCK
PB14.GPIOParameters=GPIO_Label
PB14.GPIO_Label=BMI_MISO
PB14.Mode=Full_Duplex_Master
PB14.Signal=SPI2_MISO
PB15.GPIOParameters=GPIO_Label
PB15.GPIO_Label=BMI_MOSI
PB15.Mode=Full_Duplex_Master
PB15.Signal=SPI2_MOSI
PB2.GPIOParameters=GPIO_Label
PB2.GPIO_Label=C
PB2.Signal=GPIO_Input
PB3.GPIOParameters=GPIO_Label
PB3.GPIO_Label=B_CLK
PB3.Mode=Full_Duplex_Slave
PB3.Signal=SPI1_SCK
PB4.GPIOParameters=GPIO_Label
PB4.GPIO_Label=B_MISO
PB4.Mode=Full_Duplex_Slave
PB4.Signal=SPI1_MISO
PB5.GPIOParameters=GPIO_Label
PB5.GPIO_Label=B_MOSI
PB5.Mode=Full_Duplex_Slave
PB5.Signal=SPI1_MOSI
PB6.GPIOParameters=GPIO_Label
PB6.GPIO_Label=B_CS
PB6.Signal=GPIO_Input
PB8.GPIOParameters=GPIO_Label
PB8.GPIO_Label=B2_MCU_RX
PB8.Mode=Asynchronous
PB8.Signal=USART3_TX
PB9.GPIOParameters=GPIO_Label
PB9.GPIO_Label=B2_MCU_TX
PB9.Mode=Asynchronous
PB9.Signal=USART3_RX
PC13.GPIOParameters=GPIO_Label
PC13.GPIO_Label=B2_USRLED
PC13.Signal=GPIO_Output
PC6.GPIOParameters=GPIO_Label
PC6.GPIO_Label=BMI_INT1
PC6.Signal=GPIO_Input
PF0-OSC_IN\ (PF0).Mode=HSE-External-Oscillator
PF0-OSC_IN\ (PF0).Signal=RCC_OSC_IN
PF1-OSC_OUT\ (PF1).Mode=HSE-External-Oscillator
PF1-OSC_OUT\ (PF1).Signal=RCC_OSC_OUT
RCC.HSE_VALUE=8000000
RCC.SYSCLKFreq_VALUE=16000000
board=custom

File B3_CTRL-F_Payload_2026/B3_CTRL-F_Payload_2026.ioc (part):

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Mcu.Name=STM32G071C(6-8-B)Tx
Mcu.Package=LQFP48
Mcu.UserName=STM32G071CBTx
PA13.Mode=Serial_Wire
PA13.Signal=SYS_SWDIO
PA14-BOOT0.Mode=Serial_Wire
PA14-BOOT0.Signal=SYS_SWCLK
PB3.GPIOParameters=GPIO_Label
PB3.GPIO_Label=GPS_LNA_EN
PB3.Signal=GPIO_Input
PB4.GPIOParameters=GPIO_Label
PB4.GPIO_Label=GPS_TIMEPULSE
PB4.Signal=GPIO_Input
PB5.GPIOParameters=GPIO_Label
PB5.GPIO_Label=RS_485_MODE_SW
PB5.Signal=GPIO_Output
PB6.GPIOParameters=GPIO_Label
PB6.GPIO_Label=RS485_MCU_TX
PB6.Mode=Asynchronous
PB6.Signal=USART1_TX
PB7.GPIOParameters=GPIO_Label
PB7.GPIO_Label=RS485_MCU_RX
PB7.Mode=Asynchronous
PB7.Signal=USART1_RX
PB8.GPIOParameters=GPIO_Label
PB8.GPIO_Label=GPS_SCL
PB8.Mode=I2C
PB8.Signal=I2C1_SCL
PB9.GPIOParameters=GPIO_Label
PB9.GPIO_Label=GPS_SDA
PB9.Mode=I2C
PB9.Signal=I2C1_SDA
PC13.GPIOParameters=GPIO_Label
PC13.GPIO_Label=GPS_INT
PC13.Signal=GPIO_Input
PC15-OSC32_OUT\ (PC15).GPIOParameters=GPIO_Label
PC15-OSC32_OUT\ (PC15).GPIO_Label=GPS_RST
PC15-OSC32_OUT\ (PC15).Signal=GPIO_Output
PD0.GPIOParameters=GPIO_Label
PD0.GPIO_Label=USR_LED
PD0.Signal=GPIO_Output
PF0-OSC_IN\ (PF0).Mode=HSE-External-Clock-Source
PF0-OSC_IN\ (PF0).Signal=RCC_OSC_IN
RCC.HSE_VALUE=8000000
RCC.SYSCLKFreq_VALUE=16000000
board=custom
